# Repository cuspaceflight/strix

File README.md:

This repository contains the schematics and firmware for the Martlet IV
Avionics system - Project Strix.

Project Strix is a single-board flight computer designed to carry out essential
tasks during the launch of Martlet IV. Powered by an ARM Cortex-M4, Strix is
able to perform a plethora of functions in real time, and respond to dynamic
events as they happen.

## Specification
The system must be able to
1. Carry out data acquisition for the Pulsar engine sensors.
2. Perform altimetry for the rocket for the purpose of:
	1. Finding the maximum altitude obtained by the rocket.
	2. Deploying the parachutes<sup>*</sup>.
3. Store the data obtained from 1. and 2. using a storage device in a
	protective container.
4. Transmit the data obtained from 1. and 2. to a ground station in
	real-time for the purpose of:
	1. Informing the ground support team of the Pulsar engine sensor
		data before launch (i.e. during filling operations).
	2. To aid an investigation should the rocket vehicle suffer an
		in-flight malfunction.
	3. To find out the rocket's maximum altitude in case loss of
		the rocket prevents retrieval of stored data.

<sup>*</sup>Note that a commercial off-the-shelf 'Stratologger' altimeter
	will also be wired to the parachutes and will also be able to
	deploy them for redundancy.

## Core Modules
The system is composed of several sub-modules, all connected to the central
microcontroller for unified control.

### Altimeter
The onboard altimeter uses two redundant IMUs and barometric pressure sensors
to accurately determine the altitude of the rocket.

### Sensor Front-Ends
The sensor front-ends take data from the Pulsar engine sensors and converts them
into voltages readable by the microcontroller's onboard ADCs. The subsystem
supports the following sensors:

Sensor             | Quantity | Model
------------------ | -------- | --------------------------------------------------------
Pressure Tranducer | 2        | [Omega PXM319-070GI][p_sensor]
Thermocouple       | 4        | [RS Pro K-type welded tip 1/0.315m 5m (762-1118)][t_sensor]

### Radio
The radio subsystem handles the onboard two-way ISM-band radio, which allows
Strix to both send telemetry to ground control and receive telecommands. A
modular architecture allows for precice control of output power to ensure
the rocket operates within local limits. The subsystem also contains a GPS
receiver, which assists in location of the rocket after landing.

### PSU
The modular power supply provides regulated 1.8V, 3.3V, and 12V power to the
flight computer and blackbox. Power is delivered from 2x 18650 Li-ion cells,
which can be recharged on the pad before switching to internal power.

## Design Constraints
The space allowed for the system is shown below (dimensions
in mm):

The module must also not take up the entire space; some area or a hole
must be left empty to allow other cables to pass through the rocket
(in addition to the central hole).

The module, including any batteries and mounting hardware, should have
as little mass as possible - it must weigh no more than 500g.

[spec]: https://docs.google.com/document/d/1wuNd2ukuNRVKfNca_YTkUf5Qp6ZxcXcQoBAJ7XX6a5Y
[p_sensor]: https://br.omega.com/omegaFiles/pressure/pdf/PXM309.pdf
[t_sensor]: https://docs.rs-online.com/4918/0900766b815bb169.pdf

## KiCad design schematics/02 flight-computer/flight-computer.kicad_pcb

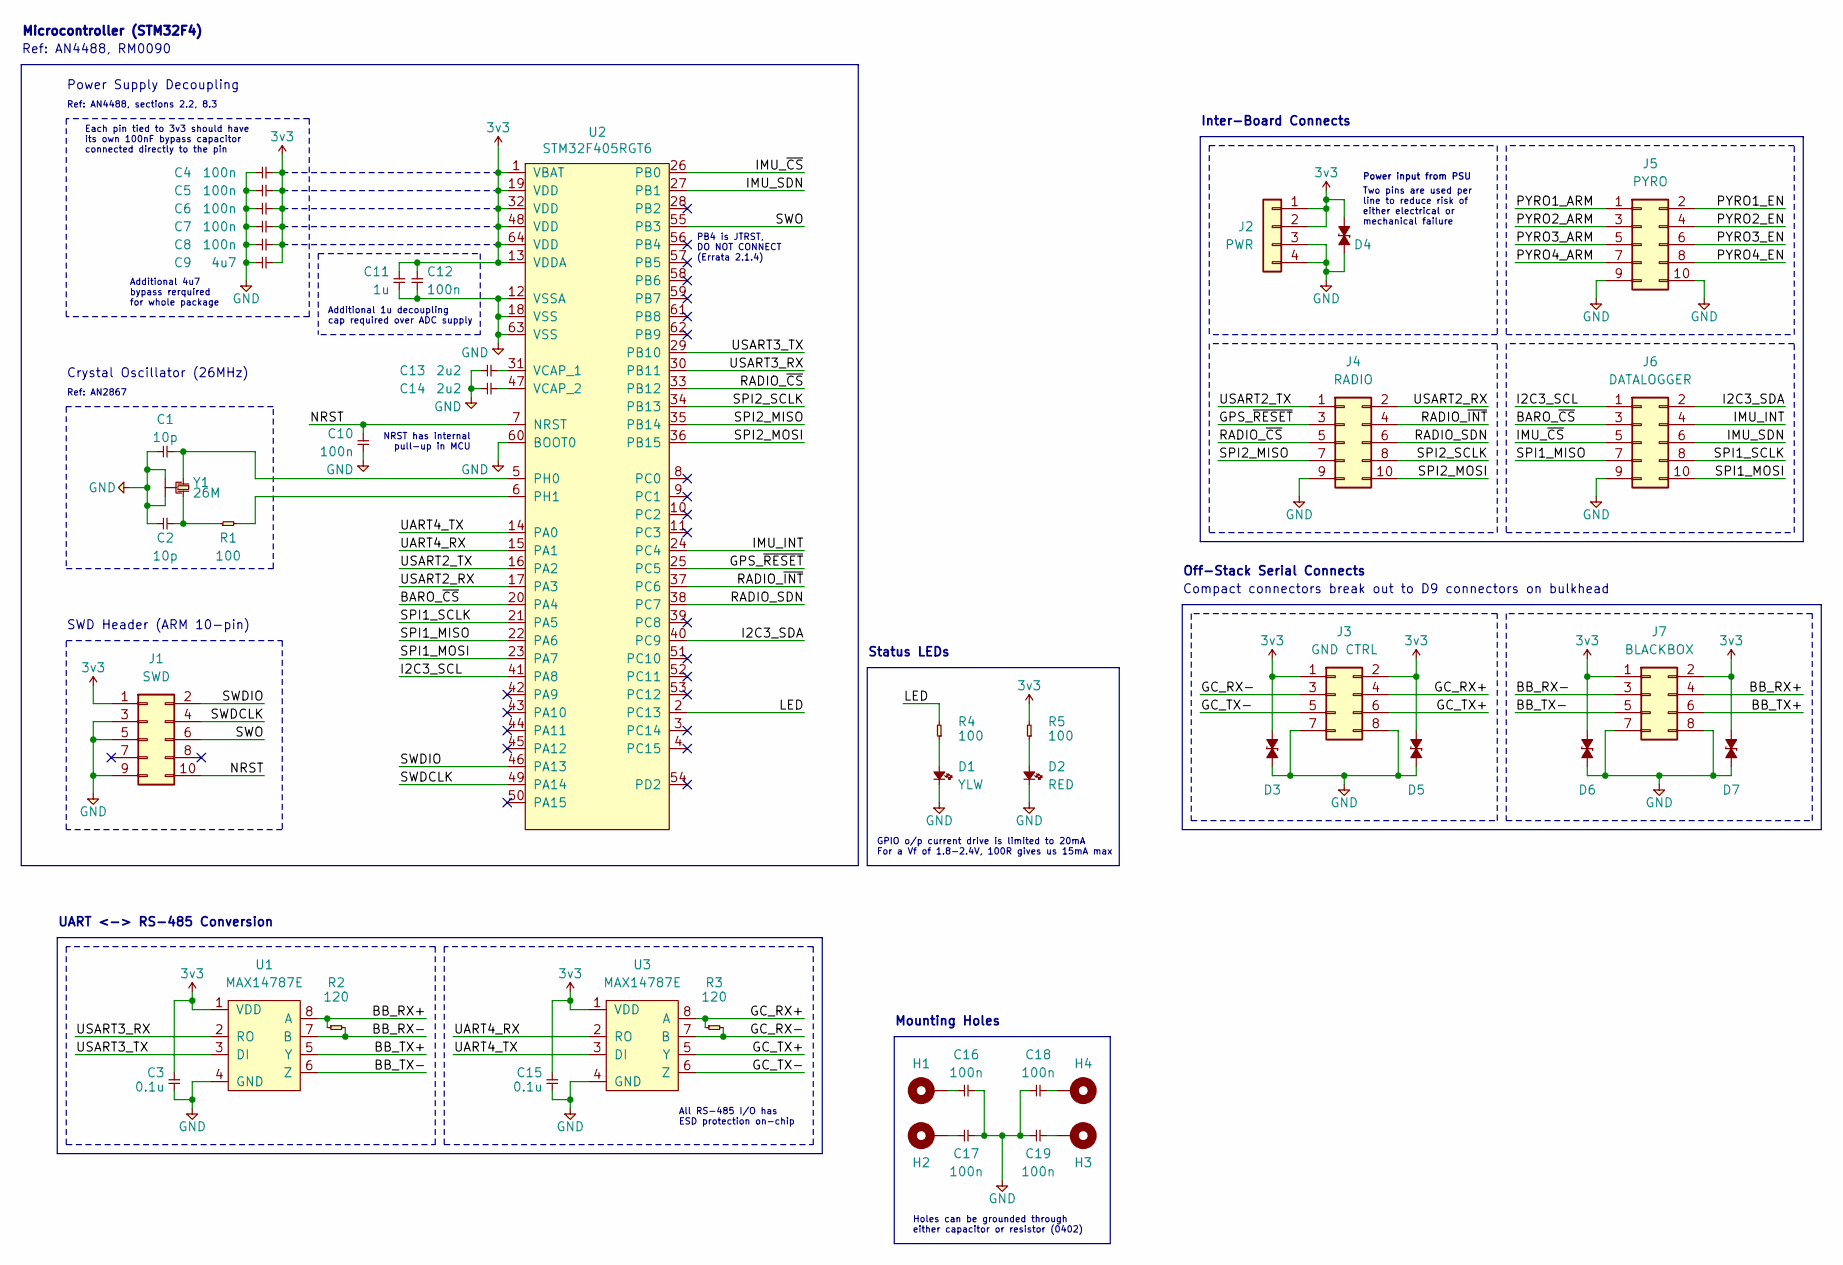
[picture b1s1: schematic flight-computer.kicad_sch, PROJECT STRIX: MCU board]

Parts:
C1, C2: 10p; C_0402; Farnell 2494183
C3, C15: 0.1u; C_0402; Farnell 2346876
C4, C5, C6, C7, C8, C10, C16, C17, C18, C19: 100n; C_0402; Farnell 2496771
C9: 4u7; C_0402; Farnell 2496771
C11: 1u; C_0402; Farnell 2346876
C12: 100n; C_0402; Farnell 2346876
C13, C14: 2u2; C_0402; Farnell 2362088
D1: YLW; LED_0603; Farnell 3796307
D2: RED; LED_0603; Farnell 3796306
D3, D4, D5, D6, D7: D_ESD; D_0402; Farnell 2368169
H1, H2, H3, H4: MountingHole_Pad
J1: SWD; Header_SWD; Farnell 2856426
J2: PWR; Molex_Nano-Fit_105313-1104
J3: GND CTRL; Molex_Nano-Fit_105314-1108
J4: RADIO; Molex_Nano-Fit_105314-1110
J5: PYRO; Molex_Nano-Fit_105314-1110
J6: DATALOGGER; Molex_Nano-Fit_105314-1110
J7: BLACKBOX; Molex_Nano-Fit_105314-1108
R1: 100; R_0402; Farnell 2447095
R2, R3: 120; R_0402; Farnell 2447103
R4, R5: 100; R_0402; Farnell 2331443
U1, U3: MAX14787E; Farnell 2528531
U2: STM32F405RGT6; Farnell 2064363
Y1: 26M; Xtal_SMD_2016; Farnell 2506952

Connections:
3v3: C3.2, C4.2, C5.2, C6.2, C7.2, C8.2, C9.2, C11.2, C12.2, C15.2, D3.2, D4.2, D5.2, D6.2, D7.2, J1.1, J2.1, J2.2, J3.1, J3.2, J7.1, J7.2, R5.2, U1.1 (VDD), U2.1 (VBAT), U2.13 (VDDA), U2.19 (VDD), U2.32 (VDD), U2.48 (VDD), U2.64 (VDD), U3.1 (VDD)
/BARO_~CS: J6.3, U2.20 (PA4)
/BB_RX+: J7.4, R2.1, U1.8 (A)
/BB_RX-: J7.3, R2.2, U1.7 (B)
/BB_TX+: J7.6, U1.5 (Y)
/BB_TX-: J7.5, U1.6 (Z)
/GC_RX+: J3.4, R3.1, U3.8 (A)
/GC_RX-: J3.3, R3.2, U3.7 (B)
/GC_TX+: J3.6, U3.5 (Y)
/GC_TX-: J3.5, U3.6 (Z)
/GPS_~RESET: J4.3, U2.25 (PC5)
/I2C3_SCL: J6.1, U2.41 (PA8)
/I2C3_SDA: J6.2, U2.40 (PC9)
/IMU_INT: J6.4, U2.24 (PC4)
/IMU_SDN: J6.6, U2.27 (PB1)
/IMU_~CS: J6.5, U2.26 (PB0)
/LED: R4.2, U2.2 (PC13)
/NRST: C10.2, J1.10, U2.7 (NRST)
/PYRO1_ARM: J5.1
/PYRO1_EN: J5.2
/PYRO2_ARM: J5.3
/PYRO2_EN: J5.4
/PYRO3_ARM: J5.5
/PYRO3_EN: J5.6
/PYRO4_ARM: J5.7
/PYRO4_EN: J5.8
/RADIO_SDN: J4.6, U2.38 (PC7)
/RADIO_~CS: J4.5, U2.33 (PB12)
/RADIO_~INT: J4.4, U2.37 (PC6)
/SPI1_MISO: J6.7, U2.22 (PA6)
/SPI1_MOSI: J6.10, U2.23 (PA7)
/SPI1_SCLK: J6.8, U2.21 (PA5)
/SPI2_MISO: J4.7, U2.35 (PB14)
/SPI2_MOSI: J4.10, U2.36 (PB15)
/SPI2_SCLK: J4.8, U2.34 (PB13)
/SWDCLK: J1.4, U2.49 (PA14)
/SWDIO: J1.2, U2.46 (PA13)
/SWO: J1.6, U2.55 (PB3)
/UART4_RX: U2.15 (PA1), U3.2 (RO)
/UART4_TX: U2.14 (PA0), U3.3 (DI)
/USART2_RX: J4.2, U2.17 (PA3)
/USART2_TX: J4.1, U2.16 (PA2)
/USART3_RX: U1.2 (RO), U2.30 (PB11)
/USART3_TX: U1.3 (DI), U2.29 (PB10)
GND: C1.1, C2.1, C3.1, C4.1, C5.1, C6.1, C7.1, C8.1, C9.1, C10.1, C11.1, C12.1, C13.1, C14.1, C15.1, C16.1, C17.1, C18.2, C19.2, D1.1, D2.1, D3.1, D4.1, D5.1, D6.1, D7.1, J1.3, J1.5, J1.9, J2.3, J2.4, J3.7, J3.8, J4.9, J5.9, J5.10, J6.9, J7.7, J7.8, U1.4 (GND), U2.12 (VSSA), U2.18 (VSS), U2.60 (BOOT0), U2.63 (VSS), U3.4 (GND), Y1.2, Y1.4
unnamed: C1.2, U2.5 (PH0), Y1.1
unnamed: C2.2, R1.1, Y1.3
unnamed: C13.2, U2.31 (VCAP_1)
unnamed: C14.2, U2.47 (VCAP_2)
unnamed: C16.2, H1.1
unnamed: C17.2, H2.1
unnamed: C18.1, H4.1
unnamed: C19.1, H3.1
unnamed: D1.2, R4.1
unnamed: D2.2, R5.1
unnamed: R1.2, U2.6 (PH1)

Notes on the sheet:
Ref: AN4488, sections 2.2, 8.3
GPIO o/p current drive is limited to 20mA For a Vf of 1.8-2.4V, 100R gives us 15mA max
Holes can be grounded through either capacitor or resistor (0402)
Ref: AN4488, RM0090
Each pin tied to 3v3 should have its own 100nF bypass capacitor connected directly to the pin
Off-Stack Serial Connects
SWD Header (ARM 10-pin)
Additional 4u7 bypass rerquired for whole package
All RS-485 I/O has ESD protection on-chip
Crystal Oscillator (26MHz)
Microcontroller (STM32F4)
Power Supply Decoupling
Compact connectors break out to D9 connectors on bulkhead
Inter-Board Connects
Status LEDs
Mounting Holes
Two pins are used per line to reduce risk of either electrical or mechanical failure
Power input from PSU
UART <-> RS-485 Conversion
PB4 is JTRST, DO NOT CONNECT (Errata 2.1.4)
Ref: AN2867
Additional 1u decoupling cap required over ADC supply
NRST has internal pull-up in MCU

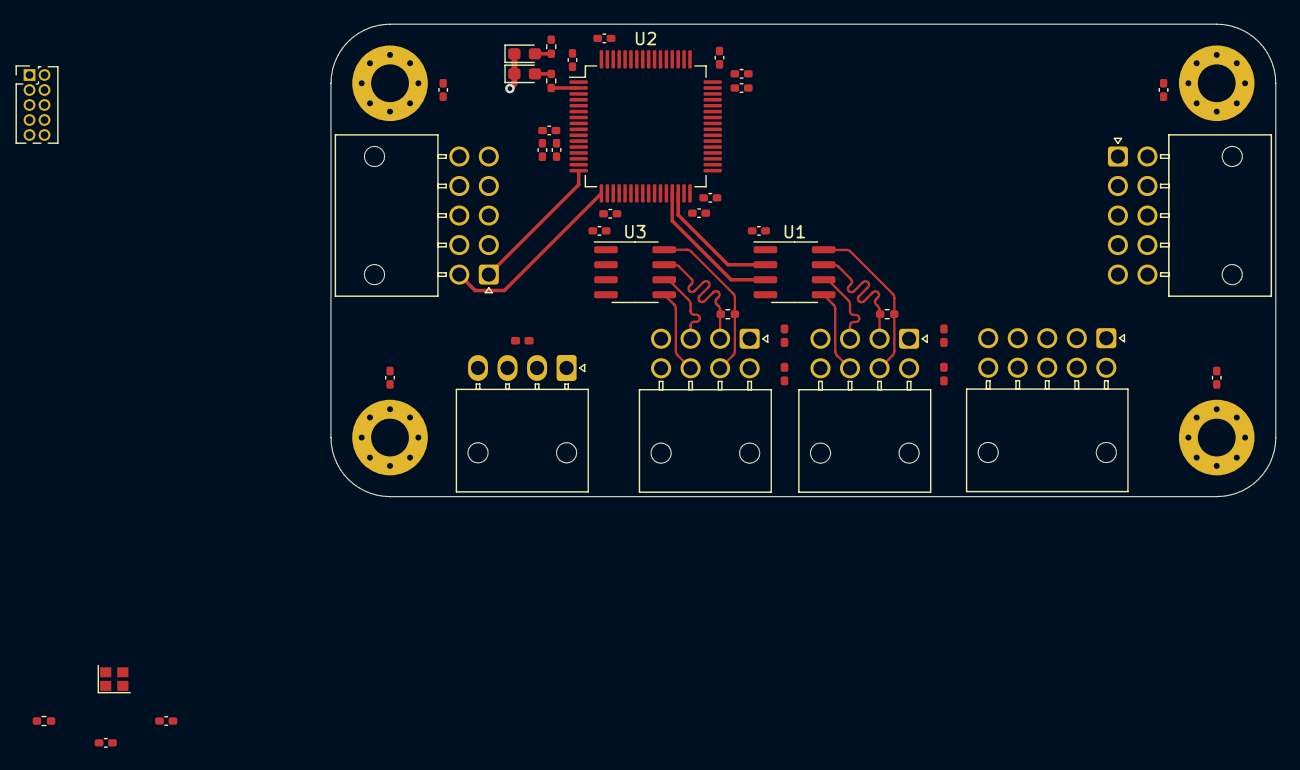
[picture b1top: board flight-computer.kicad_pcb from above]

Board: 2 copper layers, 80.0 x 40.0 mm, 46 parts (0 on the bottom side), 48 nets.

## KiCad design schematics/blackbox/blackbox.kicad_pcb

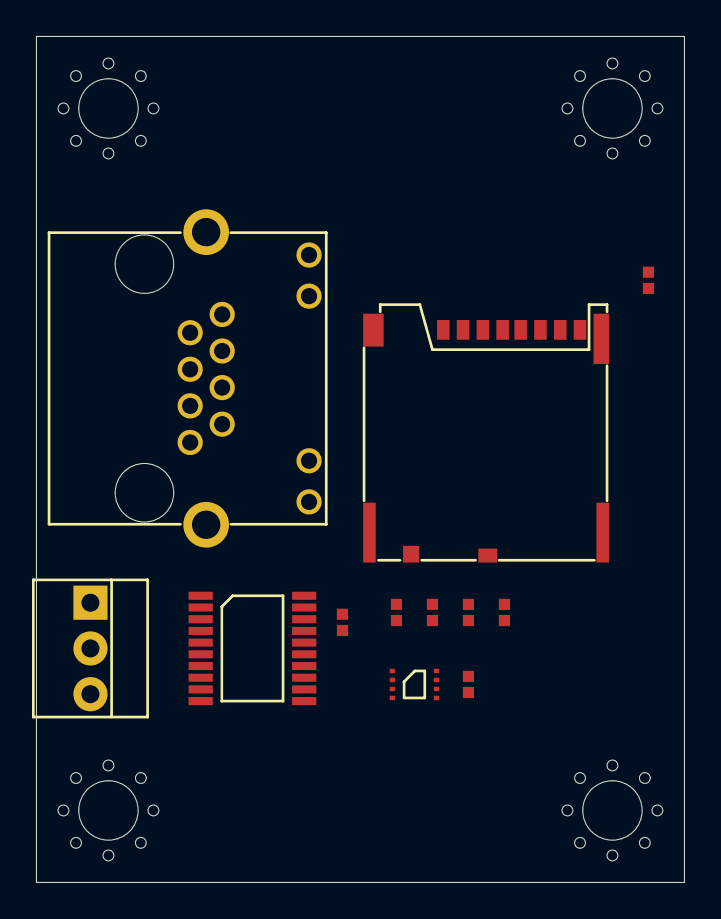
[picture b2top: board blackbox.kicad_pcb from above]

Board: 2 copper layers, 36.0 x 47.0 mm, 16 parts (0 on the bottom side), 15 nets, no tracks yet.

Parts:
C1, C2: 100n; 0402
H1, H2, H3, H4: MountingHole_Pad; M3_MOUNT
IC1: SN65LVDT14; TSSOP-20
IC2: W25Q80; UFDFN-8
J1: PWR; MOLEX-KK-254P-03
J2: RJHSE-538x; RJHSE-538X
R1, R2, R3, R4, R5: 47k; 0402
U1: MICROSD; MICROSD_MOLEX_503398-1892

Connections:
3v3: C1.1, C2.1, IC1.13, IC1.17, IC2.8, J1.2, R1.1, R2.1, R3.1, R4.1, R5.1, U1.4
/MISO: IC1.12, IC2.2, R1.2, U1.7
/MISO+: IC1.9, J2.3
/MISO-: IC1.10, J2.6
/MOSI: IC1.18, IC2.5, R5.2, U1.3
/MOSI+: IC1.3, J2.1
/MOSI-: IC1.4, J2.2
/SCLK: IC1.20, IC2.6, U1.5
/SCLK+: IC1.1, J2.8
/SCLK-: IC1.2, J2.7
/~CS1: J2.5, R4.2, U1.2
/~CS2: IC2.1, J2.4
GND: C1.2, C2.2, IC1.11, IC1.15, IC1.19, IC2.4, J1.1, J2.9, J2.10, J2.11, J2.12, J2.S1, J2.S2, U1.6, U1.9
unnamed: R2.2, U1.8
unnamed: R3.2, U1.1

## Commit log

2021-07-21 Restructure schematics; finish FC/Radio
2021-07-22 Move dl to blackbox; fix minor errors in fc
2021-08-17 Complete redesign
2021-09-17 Add temp rescue symbol while switching libs
2021-11-08 Restructure schematics in preparation for new modular system
2021-11-08 Add Strix lib
2021-11-09 Add preliminary pcb edges
2021-11-09 Add I2C pullups to flight computer
2021-12-30 First attempt at layout
2022-09-01 Add submodules to match Lychee
2022-09-01 Create empty KiCad projects for each board
2022-09-03 Create new flight computer board based on Lychee changes
2022-09-03 Update gitignore and remove backups
2022-09-03 Minor schematic revisions
2022-09-03 Early board layout (without oscillator)
2022-09-05 Further schematic work
2022-09-06 Rough datalogger schematic
